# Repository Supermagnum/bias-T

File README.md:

# bias-T
Two small  DC bias injector/extractor PCB's.
They makes it possible to power relays or other equipment without a additional separate DC cable.
DC voltages up to 60 volts is OK.

The injector board has a holder for a 1A ATO fuse. All DC copper traces should handle 1.5 A.
The RF traces are 2.5 mm wide.

The reason for the dual inductors is that in the event RF is present on the coax cable shield, the 100 uH inductor should stop it. 
All capacitors is ceramic SMD. The diode protects against reverse polarity and voltage spikes generated by relay coils.
The PCB boards measures 42X56mm.

The components should handle 1000 W RF from 160 meters to and including two meters.
That is 1.8 MHz to 145 MHz. 

IMPORTANT! 

That kind of RF power is not advised on FR4 based circuit boards!
RT/duroid® Laminates or similar products is required.
Please read: https://rushpcb.com/manufacturing-rf-and-high-frequency-boards/

scematic diagram:
https://github.com/Supermagnum/bias-T/blob/master/scema.png

For those who are lazy, the pcb boards + components is avaible here ( 100 W should be OK ):

Injector:
https://aisler.net/p/JQQXAEPC

Extractor:
https://aisler.net/p/MLCWOMDY

Dimensions:
https://github.com/Supermagnum/bias-T/blob/master/size.png

For those who wants the gerber files, and BOM's:

extractor:
https://github.com/Supermagnum/bias-T/tree/master/extractor-smd

Injector:
https://github.com/Supermagnum/bias-T/tree/master/injector-smd

Source article:
http://www.ad5x.com/images/Articles/RemoteDC%20RevA.pdf

73!

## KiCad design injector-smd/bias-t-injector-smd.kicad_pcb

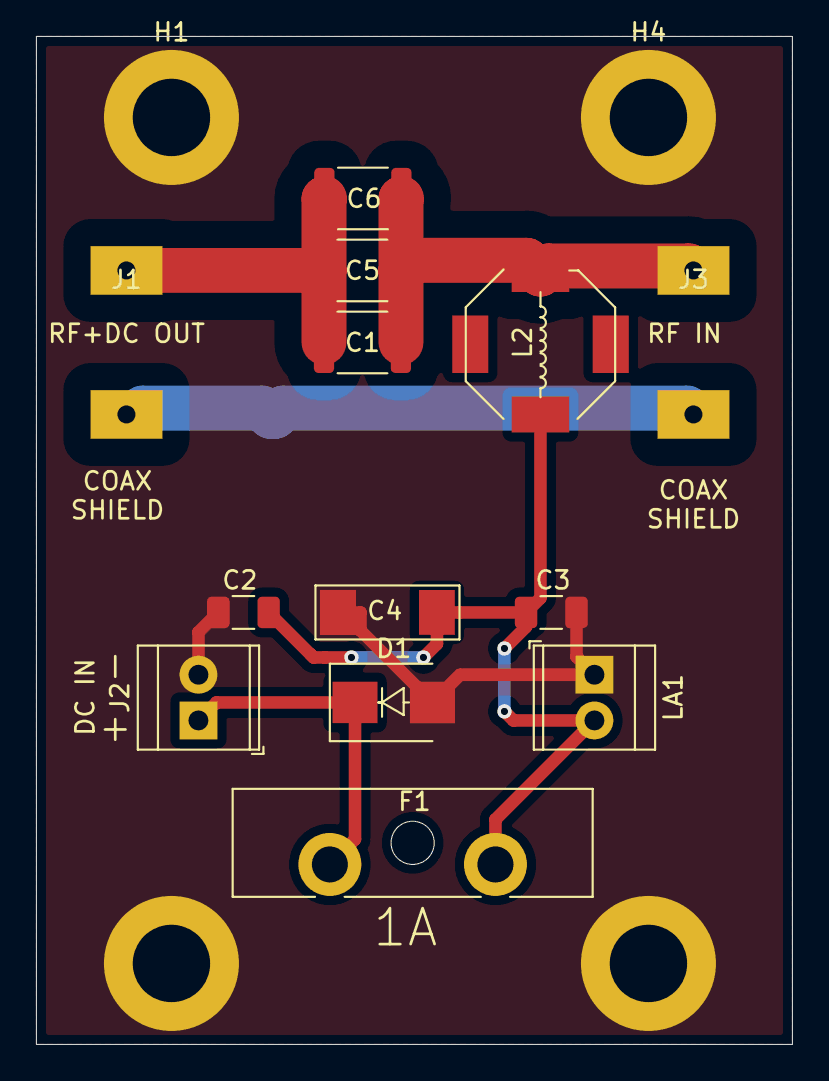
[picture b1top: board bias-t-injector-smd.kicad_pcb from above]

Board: 2 copper layers, 42.0 x 56.0 mm, 18 parts (1 on the bottom side), 6 nets.

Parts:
C1, C5, C6: 0.01uF; C_1812_4532Metric
C2: CER 10000PF 1000V X7R 1206; C_1206_3216Metric
C3: CER 100PF 1KV C0G/NP0 1206; C_1206_3216Metric
C4: CER 1000PF 1KV X7R 1808; C_1808_4520_Metric
D1: RS1MB-13-F; D_SMB
F1: Fuse; Fuseholder_Blade_ATO_Littelfuse_Pudenz_2_Pin
H1, H2, H3, H4: MountingHole_Pad; MountingHole_4.3mm_M4_DIN965_Pad
J1, J3: Conn_Coaxial; SO-239-pads
J2: Screw_Terminal_01x02; TerminalBlock_TE_282834-2_1x02_P2.54mm_Horizontal
L1, L2: SRU8045A-101Y; L_Bourns-SRU8045A-101Y_8.0x8.0mm
LA1: 282834-2; TerminalBlock_TE_282834-2_1x02_P2.54mm_Horizontal

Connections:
/GND: C2.2, C3.2, C4.2, D1.2, H1.1, H2.1, H3.1, H4.1, J2.2, L1.2, LA1.1
/RF: C1.2, C5.2, C6.2, J1.1
/RF+DC: C1.1, C5.1, C6.1, J3.1, L2.1
/RF-GND: J1.2, J3.2, L1.1
unnamed: C2.1, C3.1, C4.1, F1.1, L2.2, LA1.2
unnamed: D1.1, F1.2, J2.1

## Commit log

2020-09-01 added BOM and gerbers.
2020-09-01 picture with dimentions
2020-09-01 added diagram
2020-09-02 updated files and BOM's .
2020-09-02 added diagrams
2020-09-21 Add files via upload
    Updated RF paths to 2.5mm with
2020-09-21 Add files via upload
    Updated RF paths to 2.5mm with.
2020-09-21 Update README.md
    added with of traces.
